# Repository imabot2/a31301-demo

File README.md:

# a31301-demo

[Direct link to the video.](https://youtu.be/q6Foa80Gt3Q)

More details on [this page](https://lucidar.me).

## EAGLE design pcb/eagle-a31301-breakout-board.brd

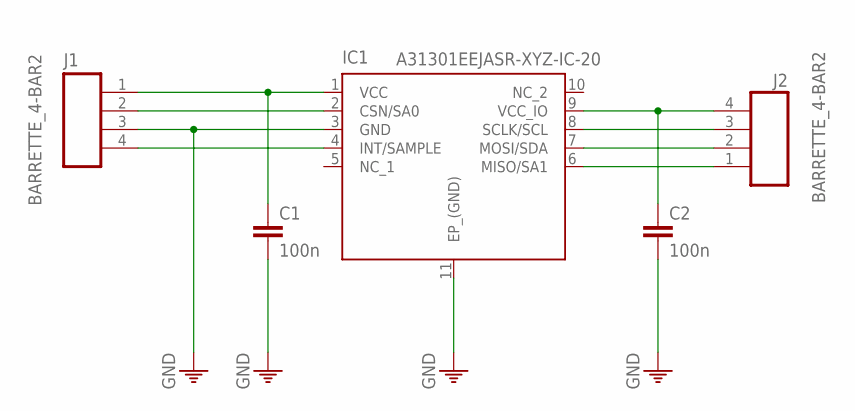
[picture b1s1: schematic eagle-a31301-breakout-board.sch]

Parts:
C1, C2: 100n; CCMS1206
IC1: A31301EEJASR-XYZ-IC-20; DFN-10
J1, J2: BARRETTE_4-BAR2; FE04

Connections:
GND: C1.2, C2.2, IC1.3 (GND), IC1.11 (EP_(GND)), J1.3
unnamed: C1.1, IC1.1 (VCC), J1.1
unnamed: IC1.2 (CSN/SA0), J1.2
unnamed: IC1.4 (INT/SAMPLE), J1.4
unnamed: IC1.6 (MISO/SA1), J2.1
unnamed: IC1.7 (MOSI/SDA), J2.2
unnamed: IC1.8 (SCLK/SCL), J2.3
unnamed: C2.1, IC1.9 (VCC_IO), J2.4

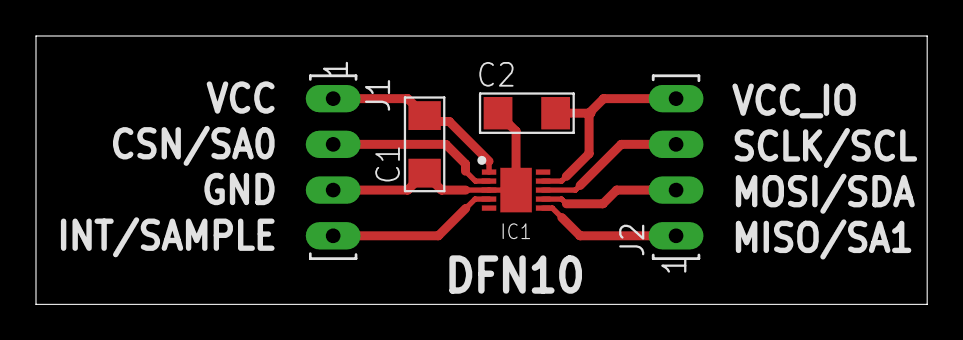
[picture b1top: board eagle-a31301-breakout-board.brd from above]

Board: 2 copper layers, 49.5 x 14.9 mm, 5 parts (0 on the bottom side), 8 nets.

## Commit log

2024-10-05 Add datasheet
